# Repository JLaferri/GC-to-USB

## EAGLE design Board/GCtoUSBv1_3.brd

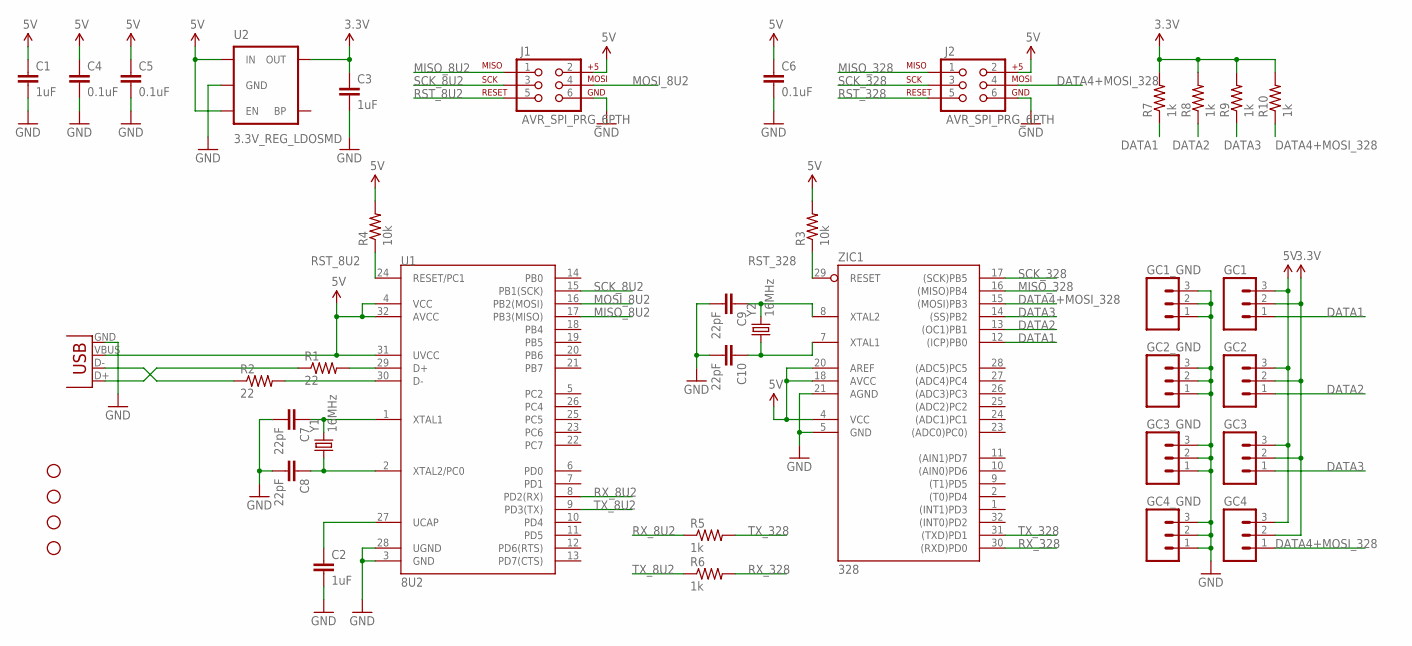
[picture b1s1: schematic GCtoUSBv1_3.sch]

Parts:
C1, C2, C3: 1uF; 0402-CAP
C4, C5, C6: 0.1uF; 0402-CAP
C7, C8, C9, C10: 22pF; 0402-CAP
GC1, GC1_GND, GC2, GC2_GND, GC3, GC3_GND, GC4, GC4_GND: M031X03_NO_SILK; 1X03_NO_SILK
J1, J2: AVR_SPI_PRG_6PTH; 2X3
JP5, JP6, JP7, JP8: STAND-OFF
R1, R2: 22; 0603-RES
R3, R4: 10k; 0603-RES
R5, R6, R7, R8, R9, R10: 1k; 0603-RES
U1: 8U2; TQFP32-08
U2: 3.3V_REG_LDOSMD; SOT23-5
X1: USB-MB-H
Y1, Y2: 16MHz; HC49US
ZIC1: 328; TQFP32-08

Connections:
3.3V: C3.1, GC1.2, GC2.2, GC3.2, GC4.2, R7.2, R8.2, R9.2, R10.2, U2.5 (OUT)
5V: C1.1, C4.1, C5.1, C6.1, GC1.3, GC2.3, GC3.3, GC4.3, J1.2, J2.2, R3.2, R4.2, U1.4 (VCC), U1.31 (UVCC), U1.32 (AVCC), U2.1 (IN), U2.3 (EN), X1.VBUS, ZIC1.4 (VCC), ZIC1.18 (AVCC), ZIC1.20 (AREF)
DATA1: GC1.1, R7.1, ZIC1.12 ((ICP)PB0)
DATA2: GC2.1, R8.1, ZIC1.13 ((OC1)PB1)
DATA3: GC3.1, R9.1, ZIC1.14 ((SS)PB2)
DATA4+MOSI_328: GC4.1, J2.4, R10.1, ZIC1.15 ((MOSI)PB3)
GND: C1.2, C2.2, C3.2, C4.2, C5.2, C6.2, C7.2, C8.2, C9.2, C10.2, GC1_GND.1, GC1_GND.2, GC1_GND.3, GC2_GND.1, GC2_GND.2, GC2_GND.3, GC3_GND.1, GC3_GND.2, GC3_GND.3, GC4_GND.1, GC4_GND.2, GC4_GND.3, J1.6, J2.6, U1.3 (GND), U1.28 (UGND), U2.2 (GND), X1.GND, ZIC1.5 (GND), ZIC1.21 (AGND)
MISO_8U2: J1.1, U1.17 (PB3(MISO))
MISO_328: J2.1, ZIC1.16 ((MISO)PB4)
MOSI_8U2: J1.4, U1.16 (PB2(MOSI))
unnamed: C9.1, Y2.2, ZIC1.8 (XTAL2)
unnamed: C10.1, Y2.1, ZIC1.7 (XTAL1)
unnamed: R1.2, U1.29 (D+)
unnamed: R2.2, U1.30 (D-)
unnamed: R1.1, X1.D+
unnamed: R2.1, X1.D-
unnamed: C7.1, U1.1 (XTAL1), Y1.2
unnamed: C8.1, U1.2 (XTAL2/PC0), Y1.1
unnamed: C2.1, U1.27 (UCAP)
RST_8U2: J1.5, R4.1, U1.24 (RESET/PC1)
RST_328: J2.5, R3.1, ZIC1.29 (RESET)
RX_8U2: R5.1, U1.8 (PD2(RX))
RX_328: R6.2, ZIC1.30 ((RXD)PD0)
SCK_8U2: J1.3, U1.15 (PB1(SCK))
SCK_328: J2.3, ZIC1.17 ((SCK)PB5)
TX_8U2: R6.1, U1.9 (PD3(TX))
TX_328: R5.2, ZIC1.31 ((TXD)PD1)

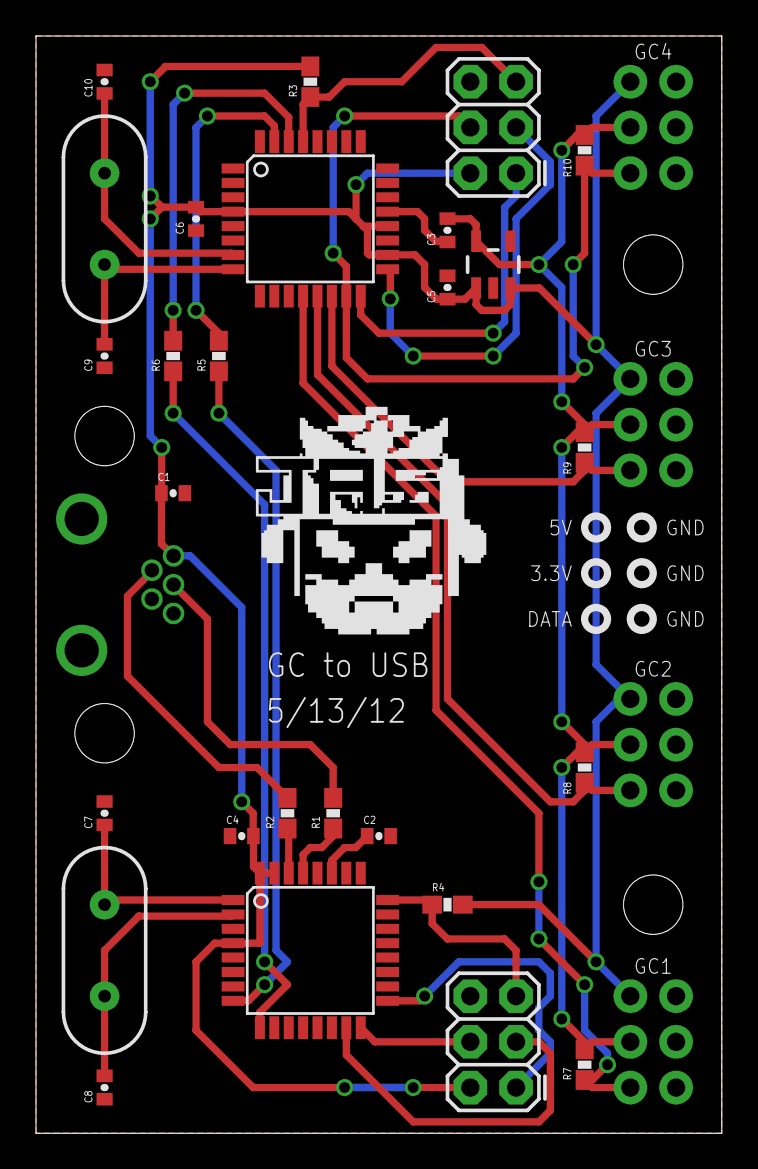
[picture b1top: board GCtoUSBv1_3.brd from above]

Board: 2 copper layers, 38.1 x 61.0 mm, 40 parts (0 on the bottom side), 27 nets.

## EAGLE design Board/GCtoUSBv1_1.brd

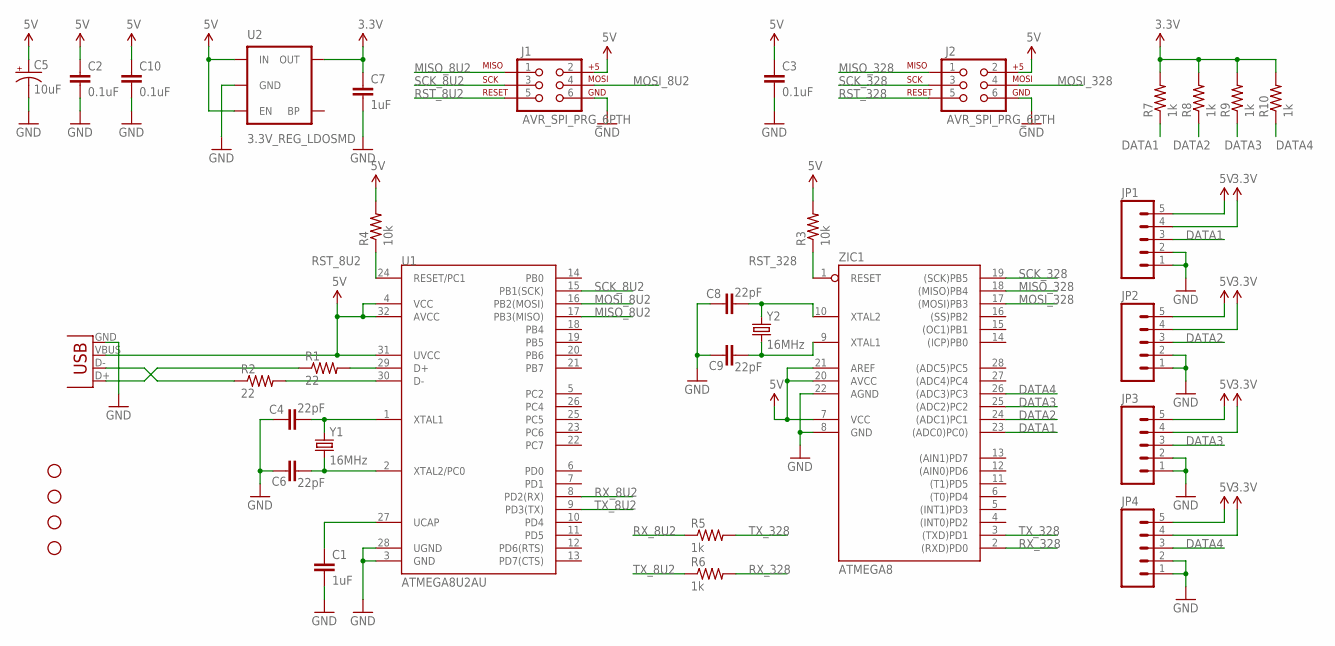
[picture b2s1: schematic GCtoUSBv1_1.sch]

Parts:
C1, C7: 1uF; CAP-PTH-5MM
C2, C3, C10: 0.1uF; CAP-PTH-SMALL
C4, C6, C8, C9: 22pF; CAP-PTH-SMALL
C5: 10uF; CPOL-RADIAL-10UF-25V
J1, J2: AVR_SPI_PRG_6PTH; 2X3
JP1, JP2, JP3, JP4: M05PTH; 1X05
JP5, JP6, JP7, JP8: STAND-OFF
R1, R2: 22; AXIAL-0.4
R3, R4: 10k; AXIAL-0.5
R5, R6, R7, R8, R9, R10: 1k; AXIAL-0.5
U1: ATMEGA8U2AU; TQFP32-08
U2: 3.3V_REG_LDOSMD; SOT23-5
X1: USBSMD; USB-MINIB
Y1, Y2: 16MHz; HC49US
ZIC1: ATMEGA8; DIL28-3

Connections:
3.3V: C7.1, JP1.4, JP2.4, JP3.4, JP4.4, R7.P$2 (2), R8.P$2 (2), R9.P$2 (2), R10.P$2 (2), U2.5 (OUT)
5V: C2.1, C3.1, C5.1 (+), C10.1, J1.2, J2.2, JP1.5, JP2.5, JP3.5, JP4.5, R3.P$2 (2), R4.P$2 (2), U1.4 (VCC), U1.31 (UVCC), U1.32 (AVCC), U2.1 (IN), U2.3 (EN), X1.VBUS, ZIC1.7 (VCC), ZIC1.20 (AVCC), ZIC1.21 (AREF)
DATA1: JP1.3, R7.P$1 (1), ZIC1.23 ((ADC0)PC0))
DATA2: JP2.3, R8.P$1 (1), ZIC1.24 ((ADC1)PC1)
DATA3: JP3.3, R9.P$1 (1), ZIC1.25 ((ADC2)PC2)
DATA4: JP4.3, R10.P$1 (1), ZIC1.26 ((ADC3)PC3)
GND: C1.2, C2.2, C3.2, C4.2, C5.2 (-), C6.2, C7.2, C8.2, C9.2, C10.2, J1.6, J2.6, JP1.1, JP1.2, JP2.1, JP2.2, JP3.1, JP3.2, JP4.1, JP4.2, U1.3 (GND), U1.28 (UGND), U2.2 (GND), X1.GND, ZIC1.8 (GND), ZIC1.22 (AGND)
MISO_8U2: J1.1, U1.17 (PB3(MISO))
MISO_328: J2.1, ZIC1.18 ((MISO)PB4)
MOSI_8U2: J1.4, U1.16 (PB2(MOSI))
MOSI_328: J2.4, ZIC1.17 ((MOSI)PB3)
unnamed: C8.1, Y2.2, ZIC1.10 (XTAL2)
unnamed: C9.1, Y2.1, ZIC1.9 (XTAL1)
unnamed: R1.P$2 (2), U1.29 (D+)
unnamed: R2.P$2 (2), U1.30 (D-)
unnamed: R1.P$1 (1), X1.D+
unnamed: R2.P$1 (1), X1.D-
unnamed: C4.1, U1.1 (XTAL1), Y1.2
unnamed: C6.1, U1.2 (XTAL2/PC0), Y1.1
unnamed: C1.1, U1.27 (UCAP)
RST_8U2: J1.5, R4.P$1 (1), U1.24 (RESET/PC1)
RST_328: J2.5, R3.P$1 (1), ZIC1.1 (RESET)
RX_8U2: R5.P$1 (1), U1.8 (PD2(RX))
RX_328: R6.P$2 (2), ZIC1.2 ((RXD)PD0)
SCK_8U2: J1.3, U1.15 (PB1(SCK))
SCK_328: J2.3, ZIC1.19 ((SCK)PB5)
TX_8U2: R6.P$1 (1), U1.9 (PD3(TX))
TX_328: R5.P$2 (2), ZIC1.3 ((TXD)PD1)

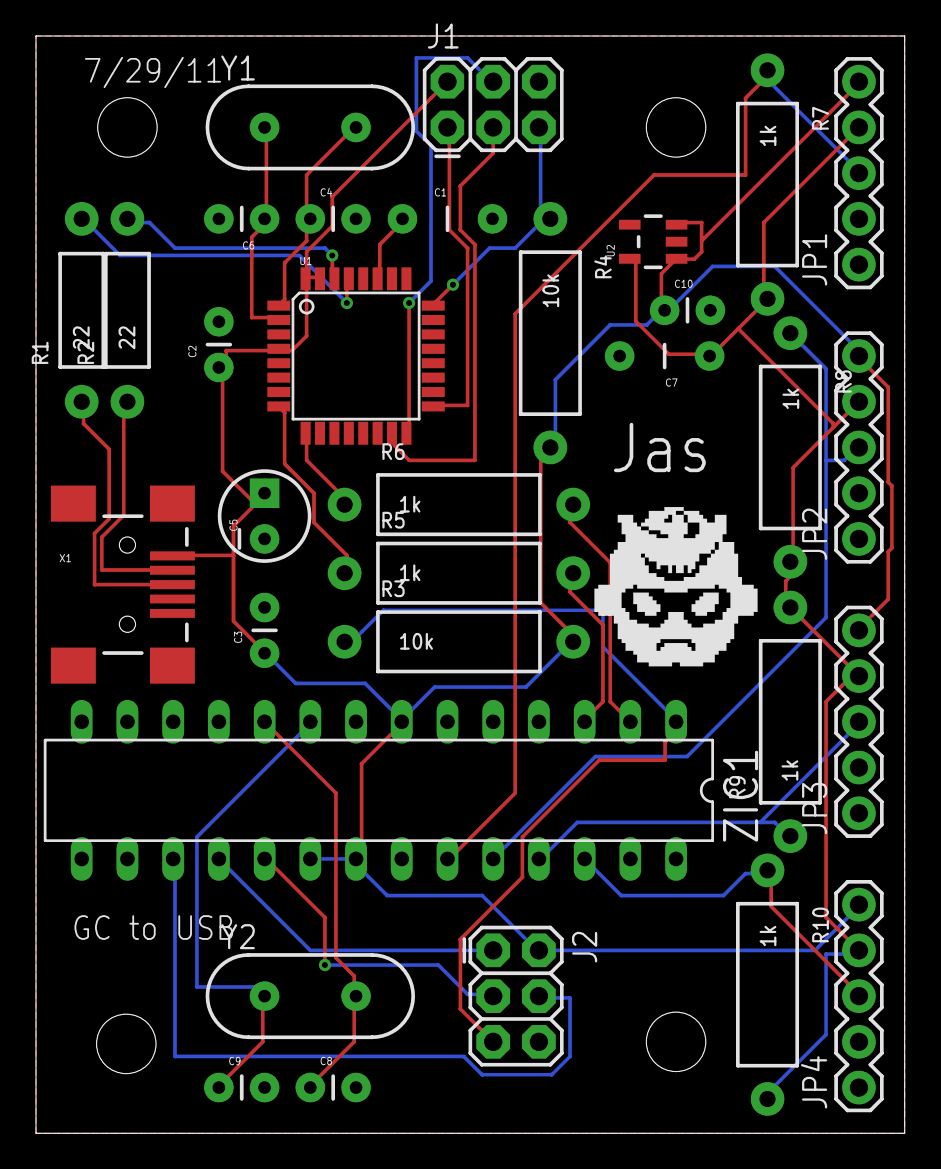
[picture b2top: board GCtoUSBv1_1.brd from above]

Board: 2 copper layers, 48.3 x 61.0 mm, 36 parts (0 on the bottom side), 28 nets.

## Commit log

2012-03-21 Finished routing new board
2012-03-21 Bottom left stud hole position was slightly off... again...
2012-03-22 Imported new logo onto PCB. Smashed components and removed part names from board.
2012-03-29 Added new icon to PCB
2012-05-02 Saved current as version 1.2 - through hole version
2012-05-05 Started work on mostly SMT version of board. Components must still be placed and routing still need be done.
2012-05-09 Finished routing on SMT version of board (Current).
2012-05-13 Moved to eagle 6.2. Completed SMT version of board - now saved as version 1.3.
2012-05-13 Forgot to add new version 1.3 files to last commit.
2012-05-13 v1.3 image
2012-05-14 Cleaned up Board folder
2012-05-17 Moved silkscreen text around a little bit in both Current and v1.3.
2012-05-19 Started work on case designed for SMT PCB.
2012-05-19 Finished new version of case with new logo, lips, and smt pcb studs.
2014-10-07 repo back up
    was working a bit on the new case
